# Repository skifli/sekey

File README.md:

# Sekey

- [Sekey](#sekey)
  - [Journal](#journal)
  - [PCB](#pcb)
    - [Schematic](#schematic)
    - [PCB Design](#pcb-design)
  - [BOM](#bom)

A FIDO2 compliant USB security key with a fingerprint scanner for safety. I made this because I've seen commercial versions of this like the YubiKey, but wanted to create my own one, which has space for a fingerprint scanner that can be used to increase security.

## Journal

Can be found in [`JOURNAL.md`](JOURNAL.md).

If you're wondering why the journal is barren, and your name isn't cyao, dm me in the Slack. If you're cyao, I already told you why teeheehee.

> [!NOTE]\
> Total time spent: **35h**

## PCB

### Schematic

### PCB Design

## BOM

$90.01 in USD.

<details closed>
<summary> Click to open (closed by default to save space)</summary>

| Component              | Description | Notes                                                                                | Quantity | Price      | Shipping | Provider   | Link                                                               |
| ---------------------- | ----------- | ------------------------------------------------------------------------------------ | -------- | ---------- | -------- | ---------- | ------------------------------------------------------------------ |
| nrf52840 Dongle        |             | Not on AliExpress                                                                    | 2        | £15.20     | £12.00   | Mouser     | [Link](https://www.mouser.co.uk/ProductDetail/949-NRF52840-DONGLE) |
| ATTINY85-20F           | SMD one     | Couldn't find this SMD one on AliExpress either                                      | 2        | £2.18      |          |            | [Link](https://www.mouser.co.uk/ProductDetail/556-ATTINY85-20SF)   |
| **Total (Mouser)**     |             |                                                                                      |          | **£29.38** |          |            |                                                                    |
|                        |             |                                                                                      |          |            |          |            |                                                                    |
| JST SH 1.00mm          | Connector   | To get a connector to solder to the PCB                                              |          | £3.82      |          | AliExpress | [Link](https://www.aliexpress.com/item/1005005787575387.html)      |
| Ceramic Capacitor      |             | Needed when writing code to the ATTiny apparently                                    |          | £3.30      |          |            | [Link](https://www.aliexpress.com/item/1005007540183265.html)      |
| Official UNO R3        |             | Needed to write code to the ATTiny, luckily very cheap                               |          | £5.82      |          |            | [Link](https://www.aliexpress.com/item/1005006967612048.html)      |
| Fingerprint Sensor     |             |                                                                                      | 2        | £11.69     | £4.68    |            | [Link](https://www.aliexpress.com/item/4000251947139.html)         |
| Resistor               | 10K         | Again when writing code, helps prevent fluctuations                                  | 1        | £0.47      | £2.46    |            | [Link](https://www.aliexpress.com/item/1005001439536671.html)      |
| Programmer Test clip   | SOP8        | To hold the ATTiny in the breadboard when writing code to it ‘cus it’s SMD of course | 1        | £0.99      | £2.75    |            |                                                                    |
| **Total (AliExpress)** |             |                                                                                      |          | **£35.98** |          |            |                                                                    |
|                        |             |                                                                                      |          |            |          |            |                                                                    |
| PCB                    |             |                                                                                      |          | £1.58      | £1.13    |            |                                                                    |
|                        |             |                                                                                      |          | **£2.71**  |          |            |                                                                    |
|                        |             |                                                                                      |          |            |          |            |                                                                    |
| **TOTAL**              |             |                                                                                      |          | **£68.07** |          |            |                                                                    |

</details>

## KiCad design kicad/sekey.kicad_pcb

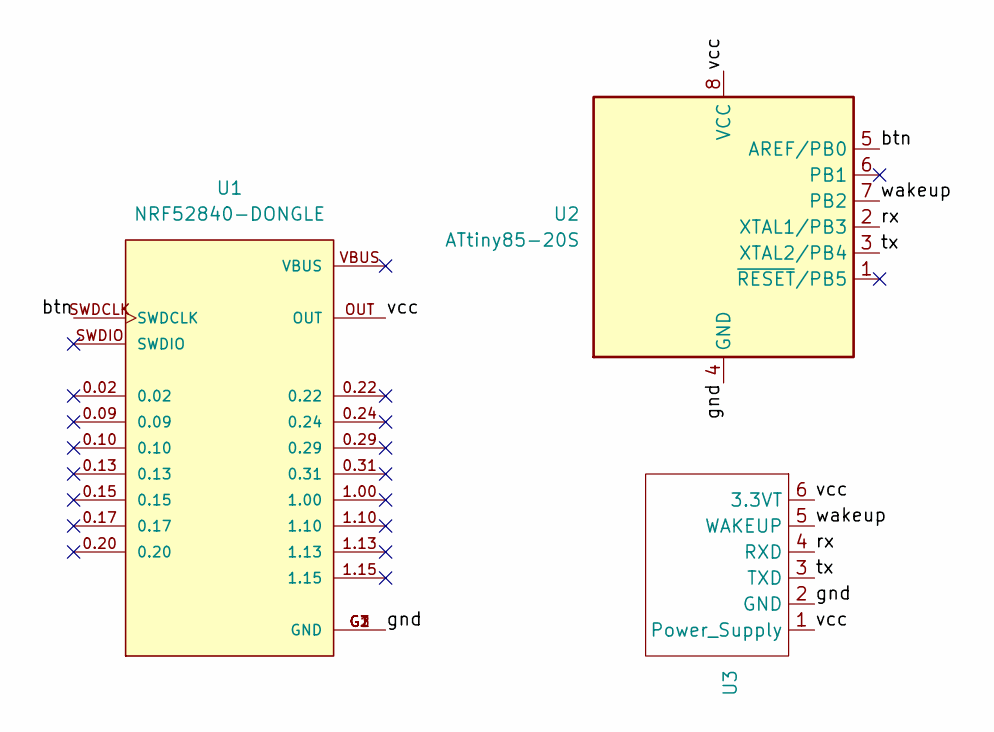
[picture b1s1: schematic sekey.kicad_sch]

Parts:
U1: NRF52840-DONGLE; MODULE_NRF52840-DONGLE; PARTREV 1.1
U2: ATtiny85-20S; SOIC-8_5.3x5.3mm_P1.27mm
U3: JST_SH_SM06B-SRSS-TB_1x06-1MP_P1.00mm_Horizontal

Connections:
/btn: U1.SWDCLK, U2.5 (AREF/PB0)
/gnd: U1.G1 (GND), U1.G2 (GND), U1.G3 (GND), U2.4 (GND), U3.2 (GND)
/rx: U2.2 (XTAL1/PB3), U3.4 (RXD)
/tx: U2.3 (XTAL2/PB4), U3.3 (TXD)
/vcc: U1.OUT, U2.8 (VCC), U3.1 (Power_Supply), U3.6 (3.3VT)
/wakeup: U2.7 (PB2), U3.5 (WAKEUP)

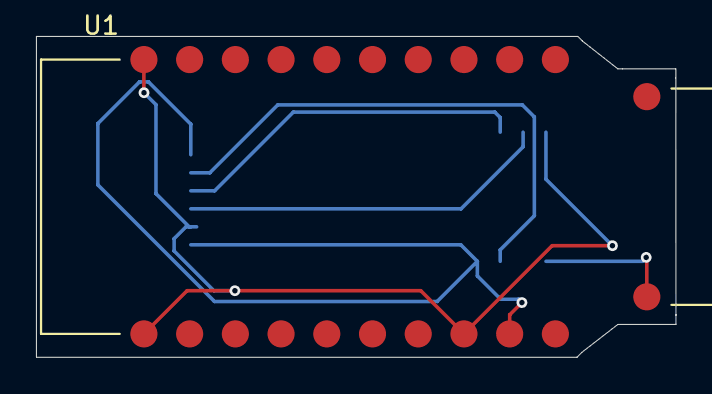
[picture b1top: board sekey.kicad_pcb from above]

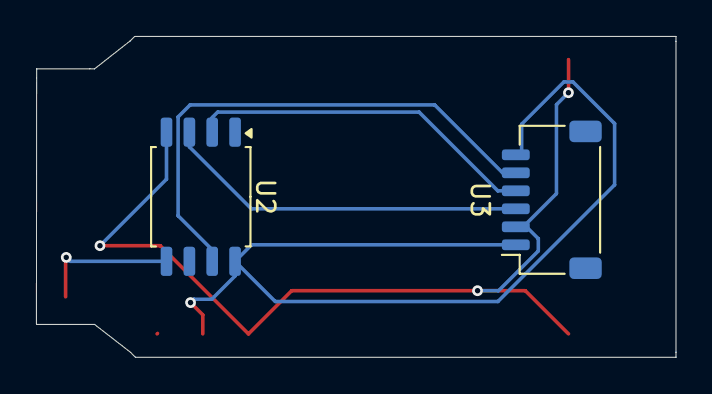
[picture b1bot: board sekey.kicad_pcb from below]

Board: 2 copper layers, 35.5 x 17.8 mm, 3 parts (2 on the bottom side), 6 nets.

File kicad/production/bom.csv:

Designator,Footprint,Quantity,Value,LCSC Part #
U1,MODULE_NRF52840-DONGLE,1,NRF52840-DONGLE,
U2,SOIC-8_5.3x5.3mm_P1.27mm,1,ATtiny85-20S,
U3,JST_SH_SM06B-SRSS-TB_1x06-1MP_P1.00mm_Horizontal,1,~,

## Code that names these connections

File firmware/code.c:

/* Will this work? Idk. Why u asking me ;-;. I can't test it rn. I do have _some_ experience in C tho: https://github.com/exeme-project/exeme-lang
*/

// My saviour: https://www.dropbox.com/scl/fo/kpbelgbmg8rojmwv3n4z1/AOLMdmIAiLb8FsjjvZLMwZg/User%20Manual%20for%20Fingerprint%20Module?e=5&preview=R502-A+fingerprint+module+user+manual-V1.3.1.pdf&rlkey=cknh86c3k4btei2t4ugsyjimn&subfolder_nav_tracking=1&dl=0

#include <SoftwareSerial.h>

// Pin definitions
#define FINGERPRINT_WAKEUP_PIN PB2 // ATtiny85 Pin 7
#define NRF_BUTTON_PIN PB0		   // ATtiny85 Pin 5
#define FINGERPRINT_RX_PIN PB3	   // ATtiny85 Pin 2
#define FINGERPRINT_TX_PIN PB4	   // ATtiny85 Pin 3

// Packet identifiers
#define FINGERPRINT_CMD_PACKET 0x01
#define FINGERPRINT_ACK_PACKET 0x07
#define FINGERPRINT_DATA_PACKET 0x02
#define FINGERPRINT_END_PACKET 0x08

// Command codes
#define FINGERPRINT_GETIMAGE 0x01
#define FINGERPRINT_IMAGE2TZ 0x02
#define FINGERPRINT_SEARCH 0x04
#define FINGERPRINT_AUTOIDENTIFY 0x32

// Response codes
#define FINGERPRINT_OK 0x00
#define FINGERPRINT_NOFINGER 0x02

SoftwareSerial fserial(FINGERPRINT_RX_PIN, FINGERPRINT_TX_PIN);

void setup() {
	// Init pins
	pinMode(FINGERPRINT_WAKEUP_PIN, INPUT_PULLUP);
	pinMode(NRF_BUTTON_PIN, OUTPUT);
	digitalWrite(NRF_BUTTON_PIN, HIGH); // Start with ze button released

	// Init fingerprint serial
	fserial.begin(57600);

	// Parar for module initialization
	delay(1000);
}

void loop() {
	// Check if finger is detected (IRQ pin goes low)
	if (digitalRead(FINGERPRINT_WAKEUP_PIN) == LOW) {
		delay(50); // Debounce
		if (digitalRead(FINGERPRINT_WAKEUP_PIN) == LOW) {
			// Use either simple authentication or auto-identify
			// simpleAuthentication();
			autoIdentify();
		}
	}
	delay(100);
}

void pressButton() {
	digitalWrite(NRF_BUTTON_PIN, LOW);	// Active low
	delay(50);							// Button press duration
	digitalWrite(NRF_BUTTON_PIN, HIGH); // Release button
	delay(1000);						// Prevent multiple triggers
}

// Way 1: Step-by-step authentication
void simpleAuthentication() {
	// Step 1: Get image
	if (sendCommand(FINGERPRINT_GETIMAGE, NULL, 0) != FINGERPRINT_OK) {
		return;
	}

	// Step 2: Convert image to template (store in buffer 1)
	uint8_t param1[] = {0x01}; // Buffer ID
	if (sendCommand(FINGERPRINT_IMAGE2TZ, param1, 1) != FINGERPRINT_OK) {
		return;
	}

	// Step 3: Search database
	// Parameters: BufferID (1), StartPage (0), PageNum (200)
	uint8_t param2[] = {0x01, 0x00, 0x00, 0xC8, 0x00};
	if (sendCommand(FINGERPRINT_SEARCH, param2, 5) == FINGERPRINT_OK) {
		pressButton();
	}
}

// Way 2: Using AutoIdentify command (simpler)
void autoIdentify() {
	// AutoIdentify command structure:
	// Header | Address | PacketID | Length | Cmd | Params | Checksum
	// EF 01 FF FF FF FF 01 00 08 32 [SecurityLevel] [StartID] [Num] [Config1] [Config2] [Checksum]
	// And a lotta magic numbers

	uint8_t packet[] = {
		0xEF,
		0x01, // Header
		0xFF,
		0xFF,
		0xFF,
		0xFF,					// Default address
		FINGERPRINT_CMD_PACKET, // Packet type
		0x00,
		0x08,					  // Length (8 bytes: cmd + params + checksum)
		FINGERPRINT_AUTOIDENTIFY, // Command
		0x03,					  // Security level (3)
		0x00,					  // Start at template 0
		0xC8,					  // Search 200 templates (0xC8 = 200)
		0x01,					  // Return status (1 = yes)
		0x01,					  // Max tries (1)
		0x00,
		0x00 // Checksum (placeholder)
	};

	// Calculate checksum (sum of bytes 6-14)
	uint16_t sum = 0;
	for (int i = 6; i <= 14; i++) {
		sum += packet[i];
	}
	packet[15] = sum >> 8;
	packet[16] = sum & 0xFF;

	// Send packet
	fserial.write(packet, sizeof(packet));

	// Freeeeeeeeeeeeeze for response
	if (readAckPacket() == FINGERPRINT_OK) {
		pressButton();
	}
}

uint8_t sendCommand(uint8_t cmd, uint8_t* params, uint8_t paramLen) {
	uint8_t packet[20]; // Max packet size we'll need (theoretically... ;-;, look i said this would be secure not... ok nevermind...)
	uint16_t sum = 0;

	// Build packet header (yes he can!)
	packet[0] = 0xEF; // Header
	packet[1] = 0x01;
	packet[2] = 0xFF; // Address
	packet[3] = 0xFF;
	packet[4] = 0xFF;
	packet[5] = 0xFF;
	packet[6] = FINGERPRINT_CMD_PACKET;

	// Packet length (cmd + params + checksum)
	uint16_t len = 1 + paramLen + 2;
	packet[7] = len >> 8;
	packet[8] = len & 0xFF;

	// Command
	packet[9] = cmd;
	sum += cmd;

	// Parameters
	for (uint8_t i = 0; i < paramLen; i++) {
		packet[10 + i] = params[i];
		sum += params[i];
	}

	// Checksum
	packet[10 + paramLen] = sum >> 8;
	packet[11 + paramLen] = sum & 0xFF;

	// Yeet packet
	fserial.write(packet, 12 + paramLen);

	// Read response
	return readAckPacket();
}

uint8_t readAckPacket() {
	uint8_t buffer[12];
	uint8_t idx = 0;
	uint32_t startTime = millis();

	// Wait for response with timeout (i dont have infinite time matey)
	while (idx < 12 && (millis() - startTime) < 2000) {
		if (fserial.available()) {
			buffer[idx++] = fserial.read();
		}
	}

	// Verify packet structure
	if (idx < 12 || buffer[0] != 0xEF || buffer[1] != 0x01 || // Header
		buffer[6] != FINGERPRINT_ACK_PACKET) {				  // ACK packet
		return 0xFF;										  // Error ;-;
	}

	// Verify checksum
	uint16_t sum = 0;
	for (uint8_t i = 6; i < 10; i++) {
		sum += buffer[i];
	}

	if (((sum >> 8) != buffer[10]) || ((sum & 0xFF) != buffer[11])) {
		return 0xFF; // Checksum error - i.e., f***
	}

	// Return confirmation code
	return buffer[9];
}

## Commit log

2025-07-28 feat: init `JOURNAL.md`
2025-07-31 feat: upload local files cus codespaces is glitching
